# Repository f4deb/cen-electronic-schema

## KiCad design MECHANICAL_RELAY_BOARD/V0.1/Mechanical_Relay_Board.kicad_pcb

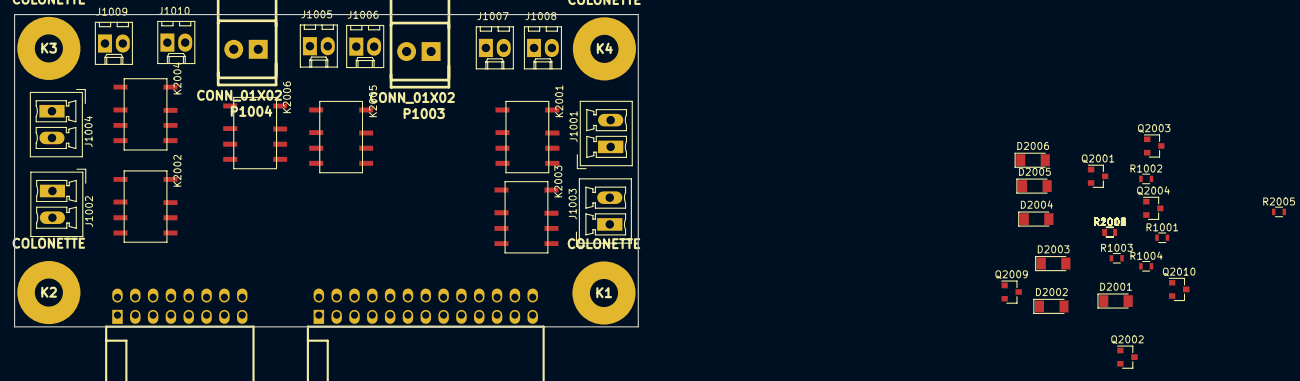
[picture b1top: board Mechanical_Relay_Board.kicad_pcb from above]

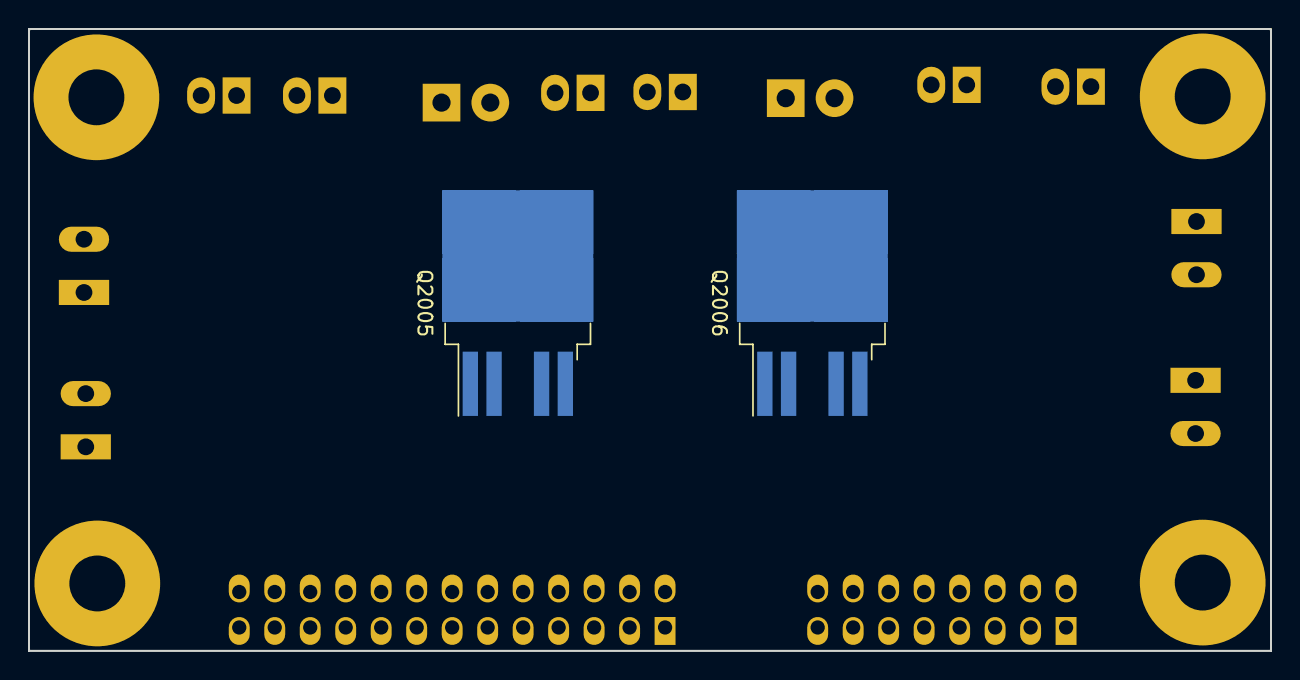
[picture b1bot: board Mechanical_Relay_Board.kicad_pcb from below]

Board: 2 copper layers, 88.9 x 44.5 mm, 52 parts (2 on the bottom side), 38 nets, no tracks yet.

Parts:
D2001, D2002, D2003, D2004, D2005, D2006: 1N4148; D_MiniMELF
J1001, J1002, J1003, J1004: CONN_01X02; PhoenixContact_MCV-G_02x3.81mm_Vertical
J1005, J1006, J1007, J1008, J1009, J1010: CONN_01X02; Molex_KK-6410-02_02x2.54mm_Straight
K1, K2, K3, K4: COLONETTE
K2001, K2002, K2003, K2004, K2005, K2006: IM03D; Relay_IMO3D
P1001: CONN_02X13; pin_socket_13x2-90
P1002: CONN_02X08; pin_socket_8x2-90
P1003, P1004: CONN_01X02; WEIDMULLER2
Q2001, Q2002, Q2003, Q2004, Q2009, Q2010: 2N7002; SOT-23
Q2005, Q2006: VN820; TO-263-4
R1001, R1002, R1003, R1004, R1005, R1006, R2001, R2002, R2003, R2004, R2005, R2006, R2009, R2010: R; R_0603

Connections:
+3V3: P1002.3, P1002.4, R1001.1, R1002.1, R1003.1, R1004.1, R1005.1, R1006.1, R2005.2, R2006.2
+5V: P1002.7, P1002.8
+5VA: D2001.1, D2002.1, D2003.1, D2004.1, D2005.1, D2006.1, K2001.1, K2002.1, K2003.1, K2004.1, K2005.1, K2006.1
+5VD: P1002.5, P1002.6
+12V: P1002.9, P1002.10
+15V: P1002.11, P1002.12, P1002.13, P1002.14
/IO1: J1005.2, P1001.21, R1006.2
/IO2: J1006.2, P1001.22, R1005.2
/IO3: J1007.2, P1001.19, R1004.2
/IO4: J1008.1, P1001.20, R1003.2
/IO5: J1009.2, P1001.17, R1002.2
/IO6: J1010.1, P1001.18, R1001.2
/IO18: P1001.4, Q2001.1, R2001.1
/IO19: P1001.3, Q2002.1, R2002.1
/IO20: P1001.6, Q2003.1, R2003.1
/IO21: P1001.5, Q2004.1, R2004.1
/IO22: P1001.8, Q2009.1, R2009.1
/IO24: P1001.10, Q2010.1, R2010.1
/Relay/REL1: J1001.2, K2001.2
/Relay/REL2: J1002.2, K2002.2
/Relay/REL3: J1003.2, K2003.2
/Relay/REL4: J1004.2, K2004.2
/Relay/REL5A: K2005.3, P1003.2
/Relay/REL5B: K2005.6, P1003.1
/Relay/REL6A: K2006.3, P1004.2
/Relay/REL6B: K2006.6, P1004.1
/Relay/SENSREL5: Q2005.2, R2005.1
GND: J1005.1, J1006.1, J1007.1, J1008.2, J1009.1, J1010.2, K2005.2, K2005.5, K2006.2, K2006.5, P1001.1, P1001.2, P1001.25, P1001.26, P1002.1, P1002.2, P1002.15, P1002.16, Q2005.1, Q2006.1, Q2009.2, Q2010.2, R2009.2, R2010.2
GNDA: K2001.3, K2002.3, K2003.3, K2004.3, Q2001.2, Q2002.2, Q2003.2, Q2004.2, R2001.2, R2002.2, R2003.2, R2004.2
unnamed: D2001.2, K2001.8, Q2001.3
unnamed: D2002.2, K2002.8, Q2002.3
unnamed: D2003.2, K2003.8, Q2003.3
unnamed: D2004.2, K2004.8, Q2004.3
unnamed: D2005.2, K2005.8, Q2009.3
unnamed: D2006.2, K2006.8, Q2010.3
unnamed: K2005.4, K2005.7, Q2005.3
unnamed: K2006.4, K2006.7, Q2006.3
unnamed: Q2006.2, R2006.1

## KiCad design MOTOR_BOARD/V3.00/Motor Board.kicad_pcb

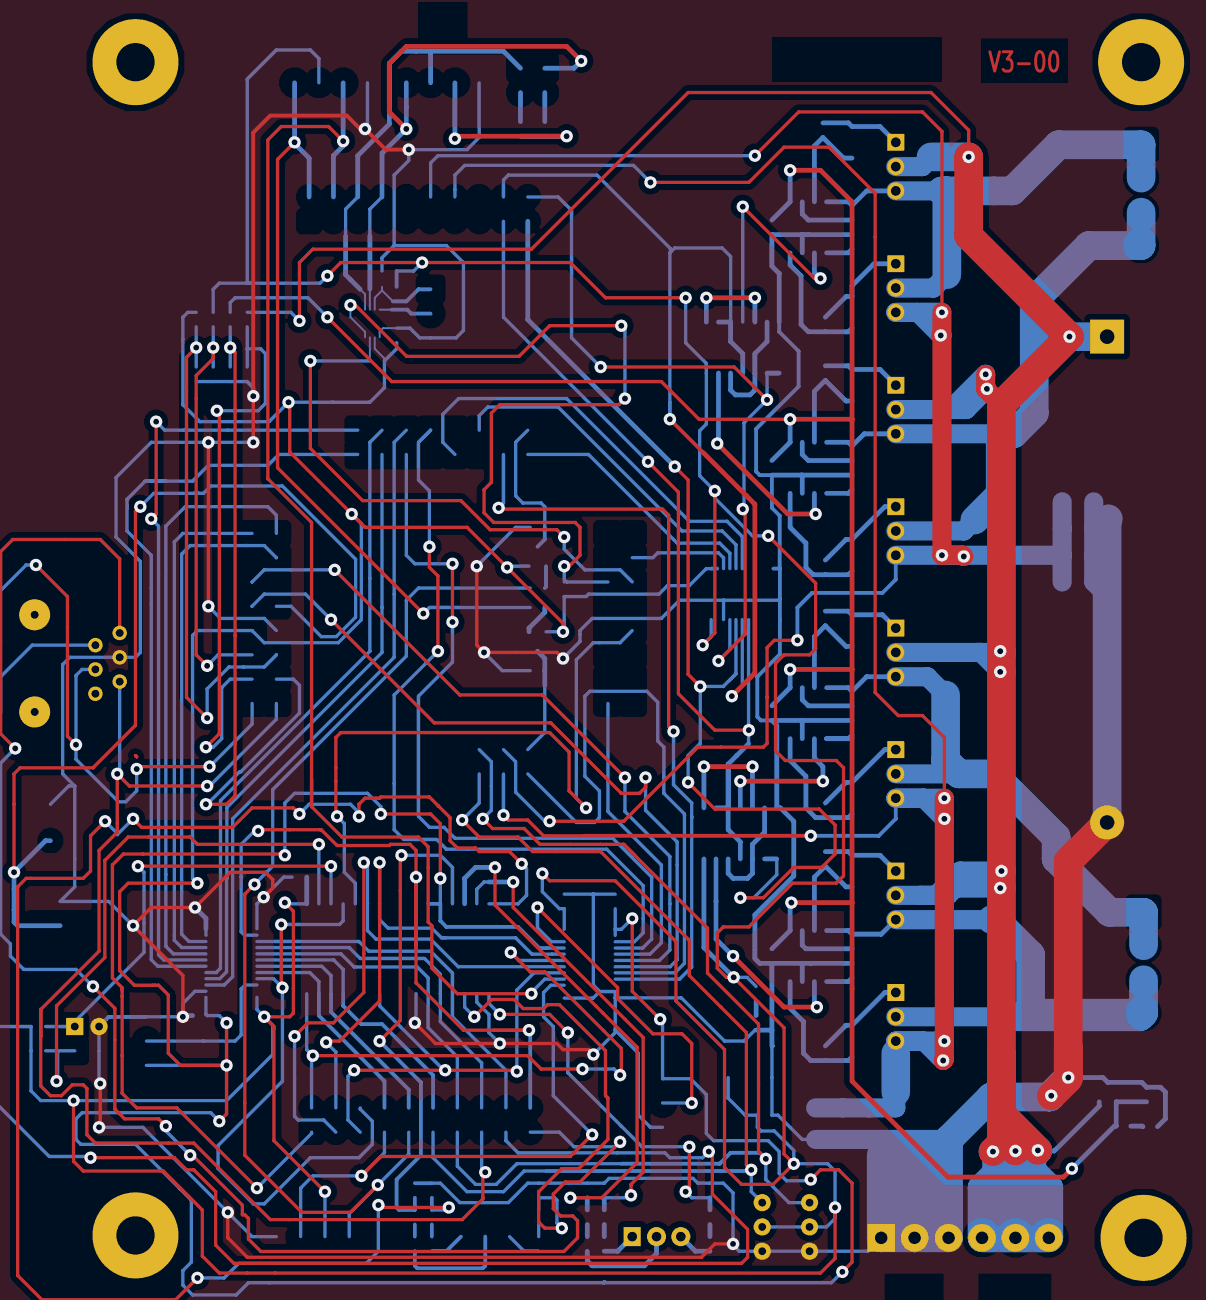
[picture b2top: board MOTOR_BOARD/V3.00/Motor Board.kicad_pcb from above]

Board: 2 copper layers, 93 parts (0 on the bottom side), 72 nets.

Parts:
C18: 47u; SM1812
C19: 4700u; CP20
C21: C; SM0603_Capa
D1: Vert; SM0603
D2, D3, D4, D5, D6, D7, D16: LED; SM0603
D8, D9, D10, D11, D12, D13, D14, D15: DIODE; SM1206
J1: RJ12; RJ12_E
K2, K4, K5: CONN_3; SIL-3
K6, K7, K8, K9: COLONETTE
P4: CONN_6; WEIDMULLER-6
P7: CAVALIER; SIL-2
Q1, Q2, Q3, Q4, Q5, Q6, Q7, Q8: MOS_N; IRFIZ48V
Q9, Q10: BC807; SOT23EBC
R5, R6, R8, R9, R12, R13, R15, R16: 47; SM0603_Resistor
R7, R10, R14, R17: 220k; SM0603_Resistor
R19: 1k; SM0603_Resistor
R20, R21, R22, R23, R24, R25, R26, R27, R28, R29, R30, R31: 1.5k; SM0603_Resistor
R32, R33: 4.7k; SM0603_Resistor
R34: 3.3k; SM0603_Resistor
R35, R36, R37, R38, R39, R40, R41, R42, R48, R49, R50, R51: R; SM0603_Resistor
R43: 200k; SM0603_Resistor
R44, R45: 2.1k; SM0603_Resistor
U3, U6: 74HC02; SO14E
U4, U5, U7, U8: LM5104; SO8E
U9: 7812; SOT23EBC
U11, U12, U13: 74LVCC3245; SSOP24
U14: PCA9306; VSSOP-8

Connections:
+3.3V: Q9.1, Q10.1, R38.1, R44.1, R45.1, U11.1, U12.1, U12.2, U13.1, U13.2, U14.2
+5VD: C18.1, C21.1, D1.1, J1.2, K4.2, K5.2, R32.1, R33.1, R37.1, R43.1, U3.14, U6.14, U11.24, U12.24, U13.24
+12V: R34.1, R36.1, U4.1, U5.1, U7.1, U8.1, U9.2
+15V: C19.1, P4.4, P4.5, P4.6, Q1.3, Q2.3, Q5.3, Q6.3, R35.1, U9.1
/MOTOR/ADC1: Q3.2, Q4.2
/MOTOR/ADC2: Q7.2, Q8.2
/MOTOR/DIR1: U3.2, U3.3, U3.11, U13.19
/MOTOR/DIR2: U6.2, U6.3, U6.11, U13.18
/MOTOR/PWM1: U3.8, U3.9, U13.21
/MOTOR/PWM2: U6.8, U6.9, U13.20
/PIC30F4013/EN2: P7.1, R33.2
/PIC30F4013/RX1: Q9.3, R50.1
/PIC30F4013/RX2: Q10.3, R51.1
GND: C18.2, C19.2, C21.2, D16.2, J1.3, K4.1, K5.1, P4.1, P4.2, P4.3, P7.2, R7.2, R10.2, R14.2, R17.2, R19.2, R23.2, R24.2, R25.2, R29.2, R30.2, R31.2, R39.2, R40.2, R41.2, R42.2, R50.2, R51.2, U3.7, U4.7, U5.7, U6.7, U7.7, U8.7, U9.3, U11.2, U11.11, U11.12, U11.13, U12.11, U12.12, U12.13, U13.11, U13.12, U13.13, U13.22, U14.1
unnamed: Q9.2, R48.2
unnamed: Q10.2, R49.2
unnamed: R28.2, R31.1
unnamed: R26.2, R29.1
unnamed: R21.2, R24.1
unnamed: R45.2, U14.4
unnamed: R44.2, U14.3
unnamed: R43.2, U14.7
unnamed: R35.2, R39.1
unnamed: R38.2, R42.1
unnamed: R37.2, R41.1
unnamed: R36.2, R40.1
unnamed: D2.1, K2.1
unnamed: D4.1, K2.3
unnamed: D6.2, R27.1
unnamed: D3.2, R21.1
unnamed: D7.2, R28.1
unnamed: D5.2, R26.1
unnamed: R27.2, R30.1
unnamed: D3.1, K2.2
unnamed: R20.2, R23.1
unnamed: R22.2, R25.1
unnamed: D4.2, R22.1
unnamed: D2.2, R20.1
unnamed: D1.2, R19.1
unnamed: U6.13, U8.6
unnamed: Q6.2, Q8.3, U8.4
unnamed: U6.1, U6.5
unnamed: U6.6, U6.10, U6.12
unnamed: D12.2, R12.2, U7.3
unnamed: D13.2, R13.2, U8.3
unnamed: R17.1, U8.5
unnamed: D15.2, R16.2, U8.8
unnamed: D16.1, R34.2
unnamed: D8.1, Q1.1, R5.1
unnamed: D10.1, Q3.1, R8.1
unnamed: D9.2, R6.2, U5.3
unnamed: D13.1, Q6.1, R13.1
unnamed: D14.1, Q7.1, R15.1
unnamed: U6.4, U7.6
unnamed: D9.1, Q2.1, R6.1
unnamed: D10.2, R8.2, U4.8
unnamed: D8.2, R5.2, U4.3
unnamed: U3.4, U4.6
unnamed: D12.1, Q5.1, R12.1
unnamed: D11.2, R9.2, U5.8
unnamed: D14.2, R15.2, U7.8
unnamed: D15.1, Q8.1, R16.1
unnamed: D11.1, Q4.1, R9.1
unnamed: U3.13, U5.6
unnamed: Q5.2, Q7.3, U7.4
unnamed: R14.1, U7.5
unnamed: R10.1, U5.5
unnamed: Q2.2, Q4.3, U5.4
unnamed: Q1.2, Q3.3, U4.4
unnamed: R7.1, U4.5
unnamed: U3.1, U3.5
unnamed: U3.6, U3.10, U3.12

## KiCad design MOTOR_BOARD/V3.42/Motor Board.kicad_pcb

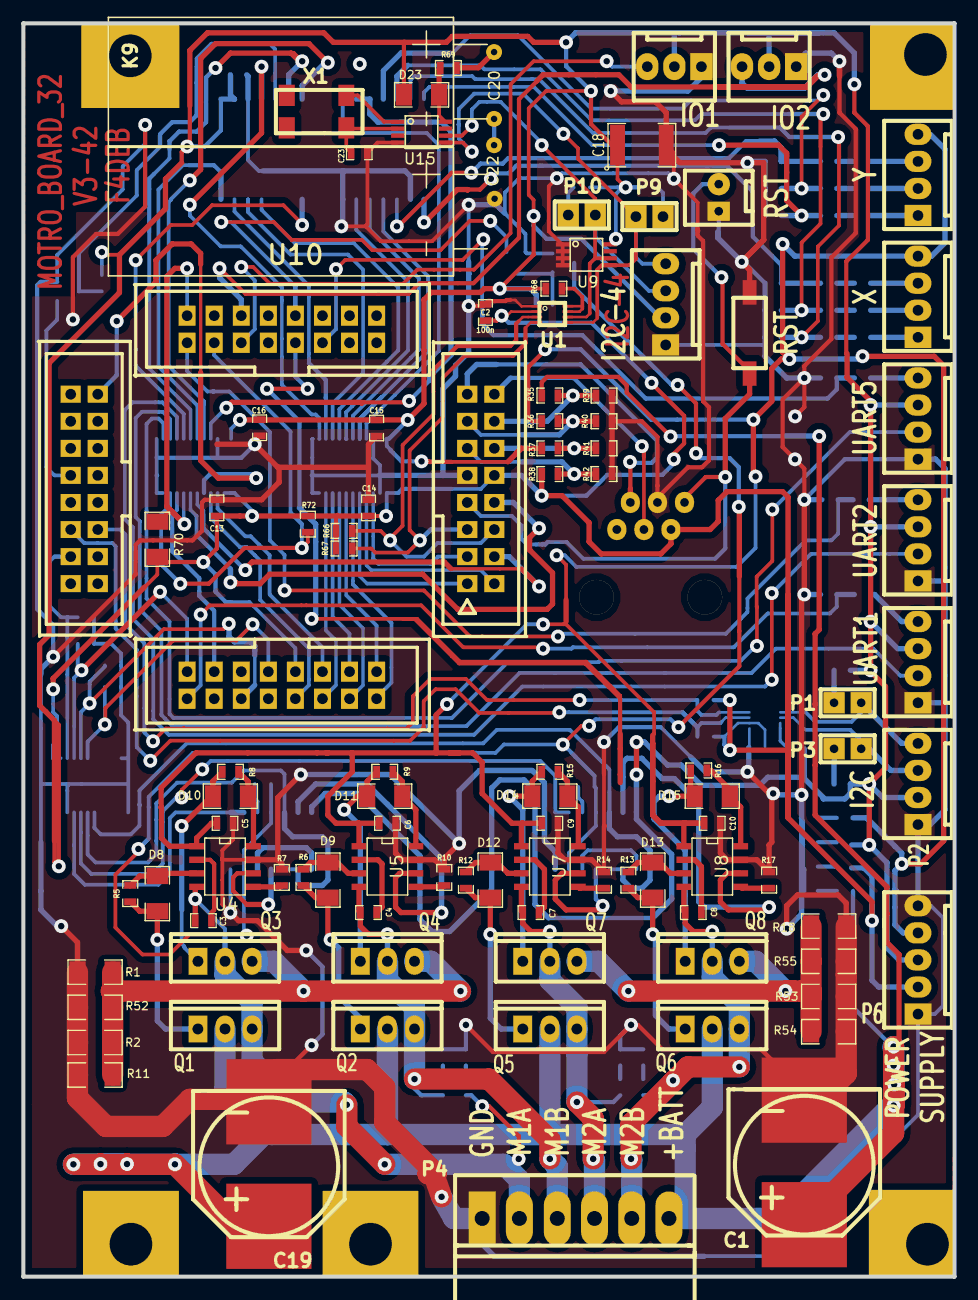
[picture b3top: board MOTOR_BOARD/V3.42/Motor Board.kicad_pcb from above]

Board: 2 copper layers, 87.4 x 117.6 mm, 172 parts (0 on the bottom side), 148 nets.

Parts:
C1, C19: 2200u; C_14x16
C2, C3, C4, C5, C6, C7, C8, C9, C10, C11, C12, C13, C14, C15, C16, C17, C21: 100n; SM0603_Capa
C18: 47u; SM1812
C20, C22: CP; C-10F
C23: C; SM0603_Capa
COLONETTE: VAL**; COLONETTE
COLONETTE#2, COLONETTE#3: VAL**; COLONETTE
D1, D16, D17, D18: VERT; SM0603
D2, D3, D4, D5, D6, D7: JAUNE; SM0603
D8, D9, D10, D11, D12, D13, D14, D15: DIODE; SM1206
D19, D20, D21, D22: LED; SM0603
D23: DIODESCH; SM1206
J1: RJ12; RJ12_E
K2, K3: CONN_4; KK-4
K4, K5: CONN_3; KK-3
K8, K9: COLONETTE
K10: CONN_2; KK-2
P1, P3, P9, P10: CAVALIER
P2, P5, P7, P8, P11: CONN_4; KK-4
P4: CONN_6; WEIDMULLER-6
P6: CONN_5; KK-5
Q1, Q2, Q3, Q4, Q5, Q6, Q7, Q8: MOS_N; IRFIZ48V
Q9, Q10, Q11: 2N7002; SOT23GDS
R1, R2, R11, R18, R52, R53, R54, R55: 0.068; SM1206
R3, R4, R20, R21, R22, R23, R24, R25, R26, R27, R28, R29, R30, R31: 1.5k; SM0603_Resistor
R5, R6, R8, R9, R12, R13, R15, R16: 47; SM0603_Resistor
R7, R10, R14, R17: 220k; SM0603_Resistor
R19: 470; SM0603_Resistor
R32: 10k; SM0603_Resistor
R33, R58: 4k7; SM0603_Resistor
R34, R48, R49, R56, R63: 1k; SM0603_Resistor
R35, R36, R37, R38: 10k 1%; SM0603_Resistor
R39, R40, R41, R42: 1k 1%; SM0603_Resistor
R43, R68: 200k; SM0603_Resistor
R44, R45, R64, R65, R66, R67: 2.1k; SM0603_Resistor
R46, R47: 3k3; SM0603_Resistor
R50, R51, R57: 1k5; SM0603_Resistor
R59, R60, R61, R62: R; SM0603_Resistor
R69: 150; SM0603_Resistor
R70: 10K; SM1206
R71, R72, R73, R74, R75, R76: 10K; SM0603_Resistor
SW2: SW_PUSH_SMALL; SW2
U1, U14: PCA9306; VSSOP-8
U2: HCTL-2032; SOJ32
U3, U6: 74HC02; SO14E
U4, U5, U7, U8: LM5104; SO8E
U9: 24C512; SSOP8
U10: PIC32MX795F512H; PIC32½64
U11, U12, U13: 74LVCC3245; SSOP24
U15: PCF8563; SSOP8
X1: CRYSTAL1; LFXTAL003000

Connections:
+3.3V: C2.1, C11.1, C12.1, C13.1, C14.1, D1.1, J1.2, P6.2, R38.1, R44.1, R45.1, R66.1, R67.1, R70.2, R71.2, R72.2, U1.2, U10.10, U10.57, U11.1, U12.1, U12.2, U13.1, U13.2, U14.2
+5VD: C15.1, C16.1, C17.1, C18.1, C21.1, D16.1, D23.1, K4.2, K5.2, P2.2, P5.3, P6.3, P7.3, P8.3, P11.2, R3.1, R4.1, R32.2, R37.1, R43.1, R63.1, R64.1, R65.1, R68.1, U2.1, U2.2, U3.14, U6.14, U9.8, U11.24, U12.24, U13.24
+12V: C5.1, C6.1, C9.1, C10.1, D17.1, K2.4, K3.4, P6.4, R36.1, U4.1, U5.1, U7.1, U8.1
+15V: C1.1, C19.1, D18.1, P4.6, Q1.3, Q2.3, Q5.3, Q6.3, R35.1
/MOTOR/DIR1: U3.2, U3.3, U3.12, U13.19
/MOTOR/DIR2: U6.2, U6.3, U6.12, U13.18
/MOTOR/M1A: C3.1, P4.2, Q1.2, Q3.3, R59.1, U4.4
/MOTOR/M1B: C4.1, P4.3, Q2.2, Q4.3, R60.1, U5.4
/MOTOR/M2A: C7.1, P4.4, Q5.2, Q7.3, R61.1, U7.4
/MOTOR/M2B: C8.1, P4.5, Q6.2, Q8.3, R62.1, U8.4
/MOTOR/MOTOREN: Q9.G, U10.24
/MOTOR/PWM1: U3.8, U3.9, U13.21
/MOTOR/PWM2: U6.8, U6.9, U13.20
/PIC30F4013/BD0: U10.60, U11.10
/PIC30F4013/BD1: U10.61, U11.9
/PIC30F4013/BD2: U10.62, U11.8
/PIC30F4013/BD3: U10.63, U11.7
/PIC30F4013/BD4: U10.64, U11.6
/PIC30F4013/BD5: U10.1, U11.5
/PIC30F4013/BD6: U10.2, U11.4
/PIC30F4013/BD7: U10.3, U11.3
/PIC30F4013/BOSC: Q11.D, R63.2, U2.5
/PIC30F4013/D0: U2.4, U11.14
/PIC30F4013/D1: U2.31, U11.15
/PIC30F4013/D2: U2.30, U11.16
/PIC30F4013/D3: U2.29, U11.17
/PIC30F4013/D4: U2.22, U11.18
/PIC30F4013/D5: U2.21, U11.19
/PIC30F4013/D6: U2.20, U11.20
/PIC30F4013/D7: U2.10, U11.21
/PIC30F4013/DI1: R75.1, U10.54, U13.5
/PIC30F4013/DI2: R76.1, U10.55, U13.6
/PIC30F4013/IO1: K5.3, U10.27
/PIC30F4013/IO2: K4.3, U10.28
/PIC30F4013/OE: U2.7, U12.20
/PIC30F4013/OSC: Q11.G, U10.40
/PIC30F4013/PGC: J1.5, U10.15
/PIC30F4013/PGD: J1.4, U10.16
/PIC30F4013/PW1: R73.1, U10.46, U13.3
/PIC30F4013/PW2: R74.1, U10.49, U13.4
/PIC30F4013/RF0: U10.58, U12.4
/PIC30F4013/RF1: U10.59, U12.3
/PIC30F4013/RST: J1.1, K10.2, SW2.1, U10.7
/PIC30F4013/RSTxy: U2.11, U2.12, U12.21
/PIC30F4013/RX1: R48.2, R50.1, U10.50
/PIC30F4013/RX2: R49.2, R51.1, U10.31
/PIC30F4013/RX5: R56.2, R57.1, U10.21
/PIC30F4013/SCL1: P2.3, P3.1, U14.6
/PIC30F4013/SCL4: P10.1, P11.3, U1.6, U9.6, U15.6
/PIC30F4013/SCL403V3: R66.2, U1.3, U10.6
/PIC30F4013/SDA1: P1.1, P2.4, U14.5
/PIC30F4013/SDA4: P9.1, P11.4, U1.5, U9.5, U15.5
/PIC30F4013/SDA403V3: R67.2, U1.4, U10.5
/PIC30F4013/SEL1: U2.6, U12.18
/PIC30F4013/SEL2: U2.26, U12.17
/PIC30F4013/TX5: R72.1, U10.29, U12.10
/PIC30F4013/U1RX: P8.4, R48.1
/PIC30F4013/U1TX: P8.2, U12.15
/PIC30F4013/U2RX: P5.4, R49.1
/PIC30F4013/U2TX: P5.2, U12.16
/PIC30F4013/U5RX: P7.4, R56.1
/PIC30F4013/U5TX: P7.2, U12.14
/PIC30F4013/X/Y: U2.32, U12.19
GND: C1.2, C2.2, C5.2, C6.2, C9.2, C10.2, C11.2, C12.2, C13.2, C14.2, C15.2, C16.2, C17.2, C18.2, C19.2, C21.2, C22.2, C23.2, D19.2, D20.2, D21.2, D22.2, J1.3, K4.1, K5.1, K10.1, P2.1, P4.1, P5.1, P6.1, P6.5, P7.1, P8.1, P11.1, Q9.S, Q10.S, Q11.S, R1.2, R2.2, R7.2, R10.2, R11.2, R14.2, R17.2, R18.2, R19.2, R23.2, R24.2, R25.2, R29.2, R30.2, R31.2, R34.2, R39.2, R40.2, R41.2, R42.2, R46.2, R47.2, R50.2, R51.2, R52.2, R53.2, R54.2, R55.2, R57.2, R73.2, R74.2, R75.2, R76.2, SW2.2, U1.1, U2.3, U2.18, U2.23, U3.7, U4.7, U5.7, U6.7, U7.7, U8.7, U9.1, U9.2, U9.3, U9.4, U10.9, U11.2, U11.11, U11.12, U11.13, U11.22, U12.11, U12.12, U12.13, U12.22, U13.11, U13.12, U13.13, U13.22, U14.1, U15.4
unnamed: D16.2, R34.1
unnamed: D17.2, R46.1
unnamed: D18.2, R47.1
unnamed: D1.2, R19.1
unnamed: P3.2, R4.2
unnamed: P10.2, R65.2
unnamed: P9.2, R64.2
unnamed: P1.2, R3.2
unnamed: R38.2, R42.1, U10.11
unnamed: R35.2, R39.1, U10.14
unnamed: R36.2, R40.1, U10.13
unnamed: R37.2, R41.1, U10.12
unnamed: U10.8, U12.7
unnamed: U10.4, U12.6
unnamed: U10.33, U12.5
unnamed: D7.2, R28.1
unnamed: D5.2, R26.1
unnamed: R27.2, R30.1, U2.13
unnamed: D7.1, K3.3
unnamed: D5.1, K3.1
unnamed: D3.1, K2.2
unnamed: R20.2, R23.1, U2.15
unnamed: R22.2, R25.1, U2.17
unnamed: D4.2, R22.1
unnamed: D2.2, R20.1
unnamed: R45.2, U10.43, U14.4
unnamed: R44.2, U10.44, U14.3
unnamed: R43.2, U14.7, U14.8
unnamed: D2.1, K2.1
unnamed: D3.2, R21.1
unnamed: R21.2, R24.1, U2.14
unnamed: D4.1, K2.3
unnamed: D6.1, K3.2
unnamed: R26.2, R29.1, U2.16
unnamed: R28.2, R31.1, U2.19
unnamed: D6.2, R27.1
unnamed: R68.2, U1.7, U1.8
unnamed: U15.1, X1.1
unnamed: R71.1, U10.51, U12.9
unnamed: R70.1, U10.32, U12.8
unnamed: D23.2, R69.1, U15.8
unnamed: C20.2, C22.1
unnamed: C20.1, R69.2
unnamed: C23.1, U15.2, X1.2
unnamed: D14.1, Q7.1, R15.1
unnamed: D15.2, R16.2, U8.8
unnamed: D13.1, Q6.1, R13.1
unnamed: D11.1, Q4.1, R9.1
unnamed: D9.2, R6.2, U5.3
unnamed: D10.1, Q3.1, R8.1
unnamed: D8.1, Q1.1, R5.1
unnamed: U6.13, U8.6
unnamed: U6.1, U6.5
unnamed: U3.1, U3.5
unnamed: R58.2, U6.10
unnamed: D12.1, Q5.1, R12.1
unnamed: D15.1, Q8.1, R16.1
unnamed: D9.1, Q2.1, R6.1
unnamed: U6.4, U7.6
unnamed: R14.1, U7.5
unnamed: D12.2, R12.2, U7.3
unnamed: C7.2, U7.2
unnamed: U3.4, U4.6
unnamed: C3.2, U4.2
unnamed: C4.2, U5.2
unnamed: D11.2, R9.2, U5.8
unnamed: R10.1, U5.5
unnamed: D13.2, R13.2, U8.3
unnamed: D14.2, R15.2, U7.8
unnamed: D8.2, R5.2, U4.3
unnamed: D10.2, R8.2, U4.8
unnamed: C8.2, U8.2
unnamed: R17.1, U8.5
unnamed: R7.1, U4.5
unnamed: U3.13, U5.6
unnamed: D20.1, R60.2
unnamed: D19.1, R59.2
unnamed: D21.1, R61.2
unnamed: D22.1, R62.2
unnamed: Q7.2, Q8.2, R18.1, R53.1, R54.1, R55.1
unnamed: Q10.D, R33.1, R58.1, U3.6, U3.11, U6.6, U6.11
unnamed: R33.2, U3.10
unnamed: Q9.D, Q10.G, R32.1
unnamed: Q3.2, Q4.2, R1.1, R2.1, R11.1, R52.1
